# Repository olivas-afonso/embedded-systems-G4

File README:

hello everyone, my first commit

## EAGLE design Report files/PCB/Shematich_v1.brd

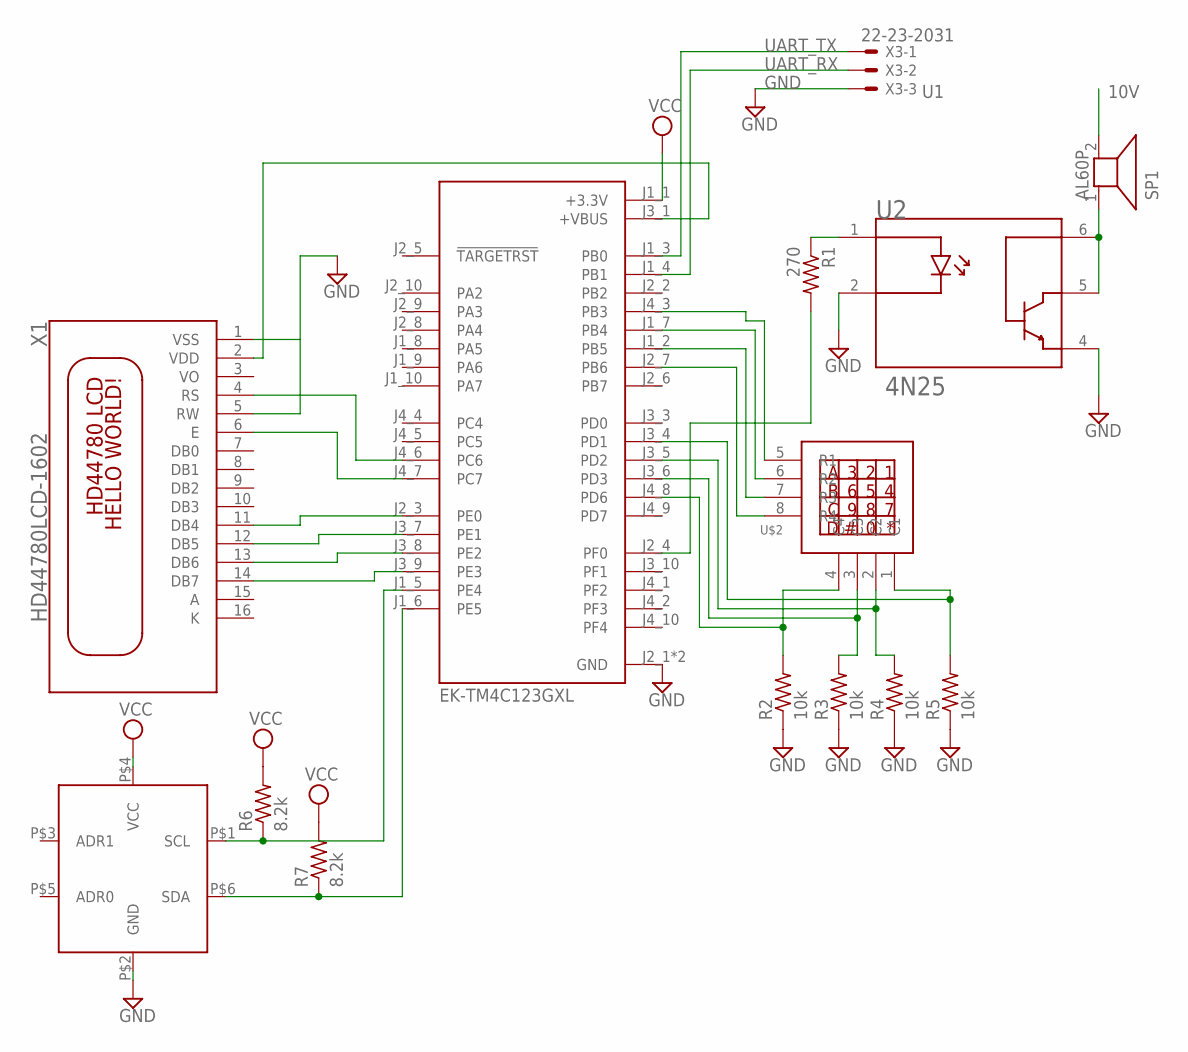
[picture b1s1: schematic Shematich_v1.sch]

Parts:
R1: 270; 0204/7
R2, R3, R4, R5: 10k; 0204/7
R6, R7: 8.2k; 0204/7
SP1: AL60P
U1: EK-TM4C123GXL; MODULE_EK-TM4C123GXL
U2: 4N25; DIP762W50P254L712H400Q6N
U$1: TMP100; SOT23-6
U$2: KEYPAD4X4
X1: HD44780LCD-1602; LCD1602
X3: 22-23-2031

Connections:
10V: SP1.2
GND: R2.1, R3.1, R4.1, R5.1, U1.J2_1 (GND), U1.J3_2 (GND), U2.2 (K), U2.4 (E), U$1.P$2 (GND), X1.1 (VSS), X1.5 (RW), X3.3
unnamed: R1.2, U1.J2_4 (PF0)
unnamed: U1.J2_3 (PE0), X1.11 (DB4)
unnamed: R3.2, U1.J3_6 (PD3), U$2.3 (C3)
unnamed: R7.1, U1.J1_6 (PE5), U$1.P$6 (SDA)
unnamed: U1.J3_7 (PE1), X1.12 (DB5)
unnamed: U1.J3_8 (PE2), X1.13 (DB6)
unnamed: U1.J3_9 (PE3), X1.14 (DB7)
unnamed: U1.J4_7 (PC7), X1.6 (E)
unnamed: U1.J4_6 (PC6), X1.4 (RS)
unnamed: R1.1, U2.1 (A)
unnamed: SP1.1, U2.5 (C), U2.6 (B)
unnamed: R2.2, U1.J4_8 (PD6), U$2.4 (C4)
unnamed: R4.2, U1.J3_5 (PD2), U$2.2 (C2)
unnamed: U1.J4_3 (PB3), U$2.5 (R1)
unnamed: U1.J1_7 (PB4), U$2.6 (R2)
unnamed: U1.J1_2 (PB5), U$2.7 (R3)
unnamed: U1.J2_7 (PB6), U$2.8 (R4)
unnamed: R5.2, U1.J3_4 (PD1), U$2.1 (C1)
unnamed: R6.1, U1.J1_5 (PE4), U$1.P$1 (SCL)
UART_RX: U1.J1_4 (PB1), X3.2
UART_TX: U1.J1_3 (PB0), X3.1
VCC: R6.2, R7.2, U1.J1_1 (+3.3V), U$1.P$4 (VCC)
VDD: U1.J3_1 (+VBUS), X1.2 (VDD)

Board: 2 copper layers, 14 parts (0 on the bottom side), 24 nets, no tracks yet.

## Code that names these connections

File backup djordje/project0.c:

//*****************************************************************************
//
// project0.c - Example to demonstrate minimal TivaWare setup
//
// Copyright (c) 2012-2017 Texas Instruments Incorporated.  All rights reserved.
// Software License Agreement
// 
// Texas Instruments (TI) is supplying this software for use solely and
// exclusively on TI's microcontroller products. The software is owned by
// TI and/or its suppliers, and is protected under applicable copyright
// laws. You may not combine this software with "viral" open-source
// software in order to form a larger program.
// 
// THIS SOFTWARE IS PROVIDED "AS IS" AND WITH ALL FAULTS.
// NO WARRANTIES, WHETHER EXPRESS, IMPLIED OR STATUTORY, INCLUDING, BUT
// NOT LIMITED TO, IMPLIED WARRANTIES OF MERCHANTABILITY AND FITNESS FOR
// A PARTICULAR PURPOSE APPLY TO THIS SOFTWARE. TI SHALL NOT, UNDER ANY
// CIRCUMSTANCES, BE LIABLE FOR SPECIAL, INCIDENTAL, OR CONSEQUENTIAL
// DAMAGES, FOR ANY REASON WHATSOEVER.
// 
// This is part of revision 2.1.4.178 of the EK-TM4C123GXL Firmware Package.
//
//*****************************************************************************

#include <stdint.h>
#include <stdbool.h>
#include "inc/hw_ints.h"   //hw ints and lcd library have a collision and dont work together
#include "inc/hw_memmap.h"
#include "inc/hw_types.h"  //
#include "driverlib/debug.h"
#include "driverlib/fpu.h"
#include "driverlib/gpio.h"
#include "driverlib/interrupt.h"
#include "driverlib/pin_map.h"
#include "driverlib/rom.h"
#include "driverlib/sysctl.h"
#include "driverlib/timer.h"
#include "driverlib/uart.h"
#include "utils/uartstdio.h"
#include "ccs/LCD.h"

#ifdef DEBUG
void
__error__(char *pcFilename, uint32_t ui32Line)
{
}
#endif


//*****************************************************************************
//
// Define pin to LED color mapping.
//
//*****************************************************************************

//*****************************************************************************
//
//! \addtogroup example_list
//! <h1>Project Zero (project0)</h1>
//!
//! This example demonstrates the use of TivaWare to setup the clocks and
//! toggle GPIO pins to make the LED's blink. This is a good place to start
//! understanding your launchpad and the tools that can be used to program it.
//
//*****************************************************************************

#define RED_LED   GPIO_PIN_1
#define BLUE_LED  GPIO_PIN_2
#define GREEN_LED GPIO_PIN_3

int var;
int letter;
uint32_t g_ui32SysClock;
char charBuffer[128];
uint8_t *charHolder;


char keyboard (void)

{
    char key[4][4] =
    {
        {'1', '2', '3', 'F'},
        {'4', '5', '6', 'E'},
        {'7', '8', '9', 'D'},
        {'A', '0', 'B', 'C'}
    };                           //define the keyboard layout
    int j,i;
    char row[] = {GPIO_PIN_3, GPIO_PIN_4, GPIO_PIN_5, GPIO_PIN_6};    //define the pins for the rows
    char line[] = {GPIO_PIN_6, GPIO_PIN_3, GPIO_PIN_2, GPIO_PIN_1};     //define the pins for the lines
    
    for (i = 0; i < 4; i++)
    {
        GPIOPinWrite(GPIO_PORTB_BASE, row[i], row[i]); //set pin in the rows to high and check all combinations
        for (j = 0; j < 4; j++) 
        {
            if (GPIOPinRead(GPIO_PORTD_BASE , line[j]) == line[j])  //check pins in the line, if the pin is high, return value of the key
                {
                letter = key[i][j];
                }
        }    
        GPIOPinWrite(GPIO_PORTB_BASE, row[i], ~row[i]); //set pin to low

    }
    return letter;
}

//*****************************************************************************
//
// Main 'C' Language entry point.  Toggle an LED using TivaWare.
//
//screen pins :input  X1:PD6   X2:PD3  X3:PD2   X4:PD1 output  Y1:PB3   Y2:PB4   Y3:PB5   Y4:PB6
//
//*****************************************************************************
int
main(void)
{

       SysCtlClockSet(SYSCTL_SYSDIV_4|SYSCTL_USE_PLL|SYSCTL_XTAL_16MHZ|SYSCTL_OSC_MAIN);  //set the clock to 50 mhz
       SysCtlPeripheralEnable(SYSCTL_PERIPH_GPIOB);
       SysCtlPeripheralEnable(SYSCTL_PERIPH_GPIOC);
       SysCtlPeripheralEnable(SYSCTL_PERIPH_GPIOD);
       SysCtlPeripheralEnable(SYSCTL_PERIPH_GPIOE);
       SysCtlPeripheralEnable(SYSCTL_PERIPH_GPIOF);
       while(!SysCtlPeripheralReady(SYSCTL_PERIPH_GPIOF))  // Enable and wait for the port to be ready for access
       {
       }

       GPIOPinTypeGPIOOutput(GPIO_PORTE_BASE, GPIO_PIN_0 | GPIO_PIN_1 | GPIO_PIN_2 | GPIO_PIN_3);
       GPIOPinTypeGPIOOutput(GPIO_PORTC_BASE, GPIO_PIN_6 | GPIO_PIN_7);    //sets pins as outputs for the screen
       GPIOPinTypeGPIOOutput(GPIO_PORTB_BASE, GPIO_PIN_3 | GPIO_PIN_4 | GPIO_PIN_5 | GPIO_PIN_6);    //sets pins as outputs for the keyboard
       GPIOPinTypeGPIOOutput(GPIO_PORTF_BASE, RED_LED|BLUE_LED|GREEN_LED);   // Configure the GPIO port for the LED operation.

       GPIOPinTypeGPIOInput(GPIO_PORTD_BASE , GPIO_PIN_6 | GPIO_PIN_1 | GPIO_PIN_2 | GPIO_PIN_3);   //sets pins D6, D3, D2, D1 as inputs for the keyboard

       GPIOPinWrite(GPIO_PORTB_BASE, GPIO_PIN_6 | GPIO_PIN_1 | GPIO_PIN_2 | GPIO_PIN_3, 0x000); //set B pins to low

       char test[] = "IM ALIVE";
       char test2[] = "GG";

       Lcd_Init();
       SysCtlDelay(2000000);
       Lcd_Clear();
       SysCtlDelay(2000000);
       Lcd_Write_String(test);



    SysCtlDelay(200000);

    while(1)
    {

        GPIOPinWrite(GPIO_PORTF_BASE, RED_LED|BLUE_LED|GREEN_LED, RED_LED); // Turn on the LED

        SysCtlDelay(2000000);
        test2[0] = keyboard();
        Lcd_Write_String(test2);

        GPIOPinWrite(GPIO_PORTF_BASE, RED_LED|BLUE_LED|GREEN_LED, BLUE_LED); // Turn on the LED

        SysCtlDelay(2000000);
        SysCtlDelay(8000000);
        Lcd_Clear();
        SysCtlDelay(2000000);

    }
}

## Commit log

2023-11-22 Create README
    initial creation
2023-11-23 change name of datasheet
2023-11-23 TIVA launchpad pinout
2023-11-23 pcb stuff
2023-11-27 shematic 2
2023-11-27 shematic 3
2023-11-27 final schematic
2023-11-27 final final schematic
2023-11-29 final final final schematic (ready for hardware)
2023-11-30 datasheets and guides
2023-12-07 my first commit
2023-12-12 working LCD project
2023-12-14 i2c working project ( with printing temp on lcd)
2023-12-21 stuff
2023-12-21 documents
2023-12-21 LCD_works
2023-12-21 test lcd export
2023-12-27 keyboard working
2023-12-29 uart project thing (half works)
    it has attemp of interrupts but failed, tries to print onto lcd but i dont think it worked
2023-12-29 buzzer to test; updated gantt
2023-12-31 schematic updated
2024-01-04 buzzer working
2024-01-05 (almost there)
2024-01-05 Create cutting strings
2024-01-06 buzzer exported
2024-01-07 quase quase falta comments
2024-01-07 charts
2024-01-08 FINAL PROJECT
2024-01-08 final commit
2024-01-08 Final Project Commit
2024-01-08 Final submit
